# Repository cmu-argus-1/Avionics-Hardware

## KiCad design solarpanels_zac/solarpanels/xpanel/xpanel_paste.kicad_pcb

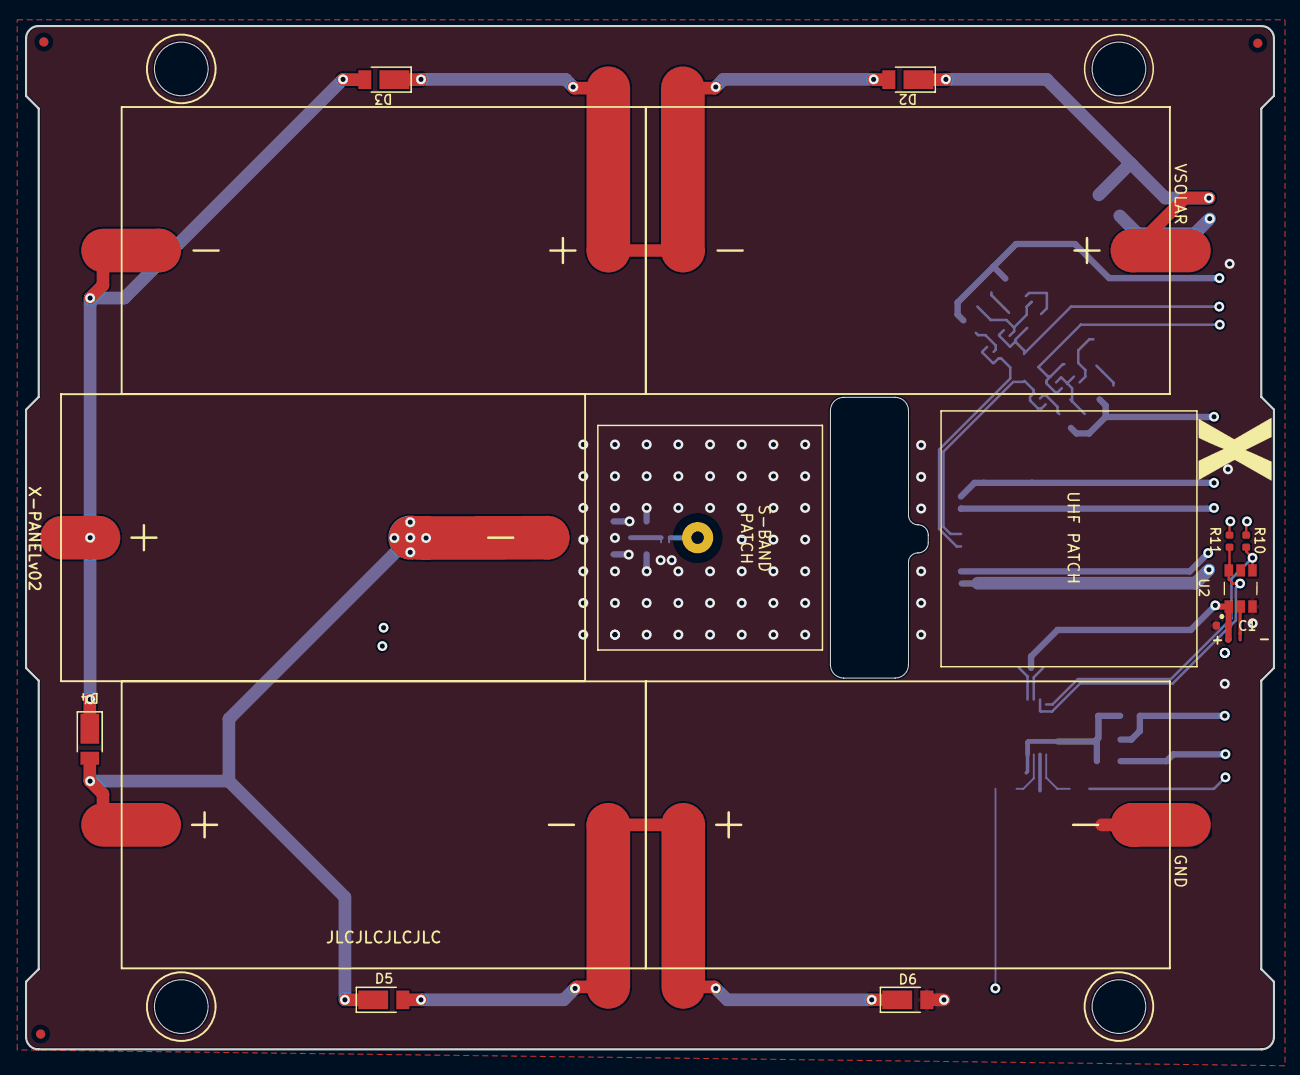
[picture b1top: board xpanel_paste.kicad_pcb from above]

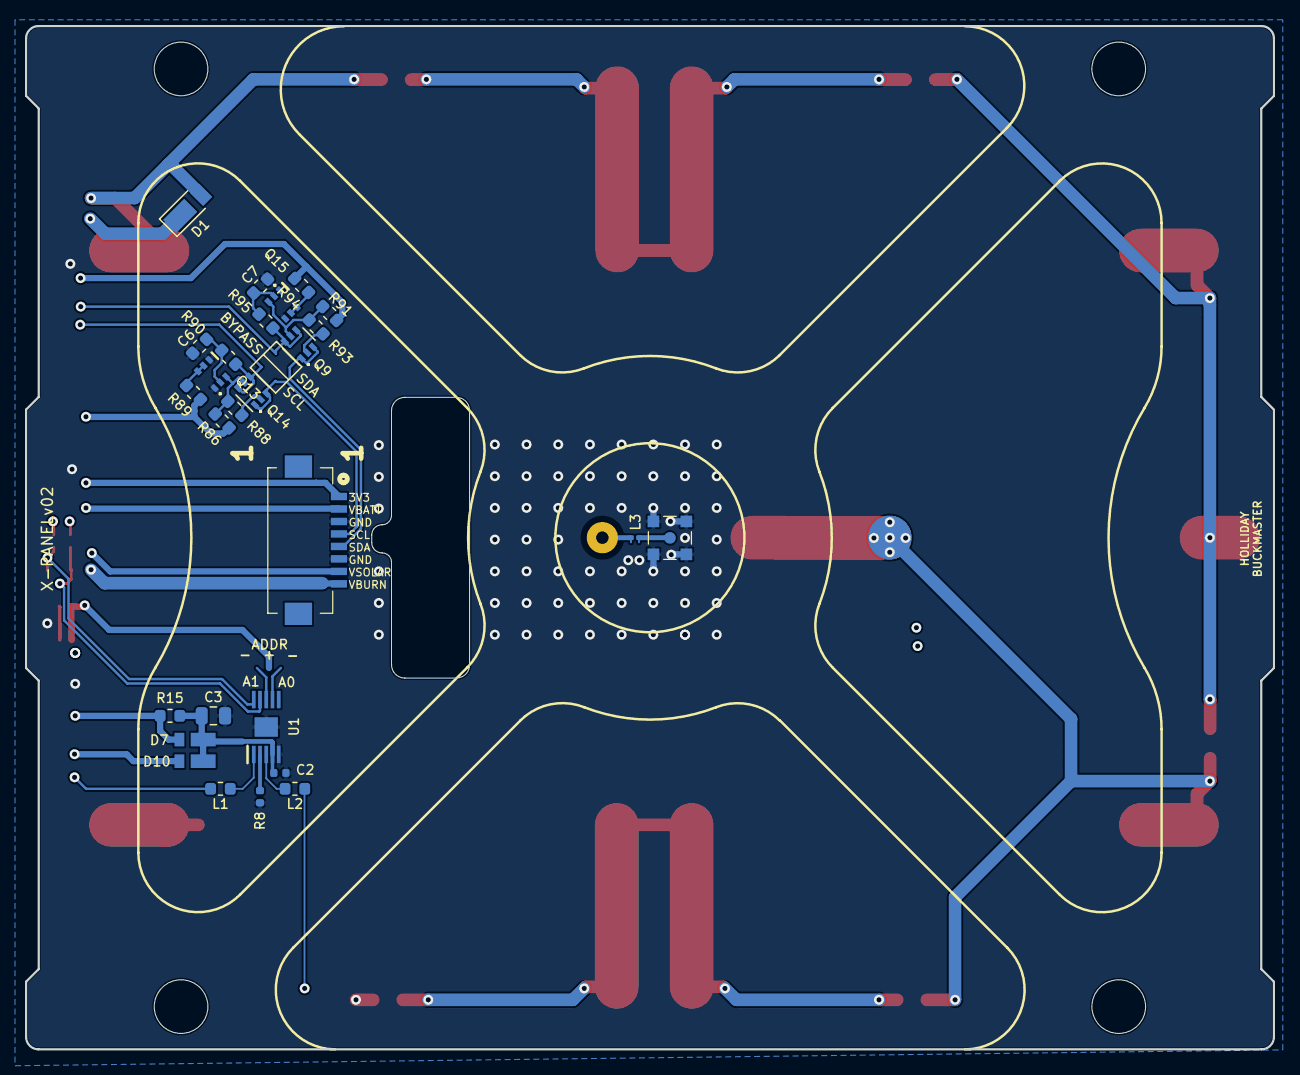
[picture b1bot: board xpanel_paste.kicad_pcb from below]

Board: 6 copper layers, 100.0 x 82.0 mm, 50 parts (27 on the bottom side), 29 nets.

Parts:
AE1: SXP.18.4.A.02
C1, C2: 0.1uF; C_0402_1005Metric
C3: 10uF; C_0805_2012Metric
C6, C7: 10nF; C_0603_1608Metric
D1, D2, D3, D4, D5, D6: SBD; D_PowerDI-123
D7, D10: SBD; SOD-323HE
FID1, FID2, FID3: Fiducial; Fiducial_0.75mm_Mask1.5mm
H1, H2, H3, H4: MountingHole; MountingHole_4.3mm_M4
J1: XF3M(1)-0815-1B; XF3M108151B
J2: MMCX_SMD; 0734152063
L1, L2: TBD; L_0603_1608Metric
L3: TBD; L_0201_0603Metric
Q9, Q14: MBT2222ADW1T1; SOT-363_SC-70-6
Q13, Q15: BSS138DWQ-7
R8: 0; R_0402_1005Metric
R10, R11: 10K; R_0402_1005Metric
R15: 0; R_0603_1608Metric
R86, R89, R91, R94: 10K; R_0603_1608Metric
R88, R93: 600; R_0603_1608Metric
R90, R95: 100K; R_0603_1608Metric
Ref**: Val**; xpanel
SC1, SC2, SC3, SC5, SC6: SM141K06L
U1: DRV8830DGQR
U2: TSL2561

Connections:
+3V3: C1.1, D7.2, J1.1, R10.2, R11.2, R15.1, R86.1, R89.2, R91.1, R94.2, U2.1
/VSOLAR: D1.1, J1.7
/torque-coil: L1.1, L2.1
GND: C1.2, C2.2, C3.2, C6.2, C7.2, D6.2, J1.3, J1.6, J2.2, J2.3, J2.4, J2.5, Q13.1, Q13.4, Q15.1, Q15.4, R8.1, SC6.2, U1.5, U1.11, U2.3
unnamed: AE1.1, L3.1
unnamed: C2.1, C3.1, D7.1, D10.1, R15.2, U1.4
unnamed: J2.1, L3.2
unnamed: C6.1, Q13.5, R90.1
unnamed: C7.1, Q15.2, R95.1
unnamed: D1.2, D2.1, SC1.1
unnamed: D2.2, D3.1, SC1.2, SC2.1
unnamed: D3.2, D4.1, SC2.2, SC3.1
unnamed: D4.2, D5.1, SC3.2, SC5.1
unnamed: D5.2, D6.1, SC5.2, SC6.1
unnamed: J1.MP1, J1.MP2
unnamed: L1.2, U1.1
unnamed: L2.2, U1.3
unnamed: Q9.2, R93.1
unnamed: Q13.2, Q13.3, R89.1
unnamed: Q13.6, Q14.5, R86.2, R88.1
unnamed: Q14.2, R88.2
unnamed: Q9.5, Q15.3, R91.2, R93.2
unnamed: Q15.5, Q15.6, R94.1
unnamed: R8.2, U1.2
SCL: Q14.4, Q14.6, R10.1, R90.2, U1.10, U2.4
SCL1_b4iso: J1.4, Q14.1, Q14.3
SDA: Q9.4, Q9.6, R11.1, R95.2, U1.9, U2.6
SDA1_b4iso: J1.5, Q9.1, Q9.3
VBATT: D10.2, J1.2
